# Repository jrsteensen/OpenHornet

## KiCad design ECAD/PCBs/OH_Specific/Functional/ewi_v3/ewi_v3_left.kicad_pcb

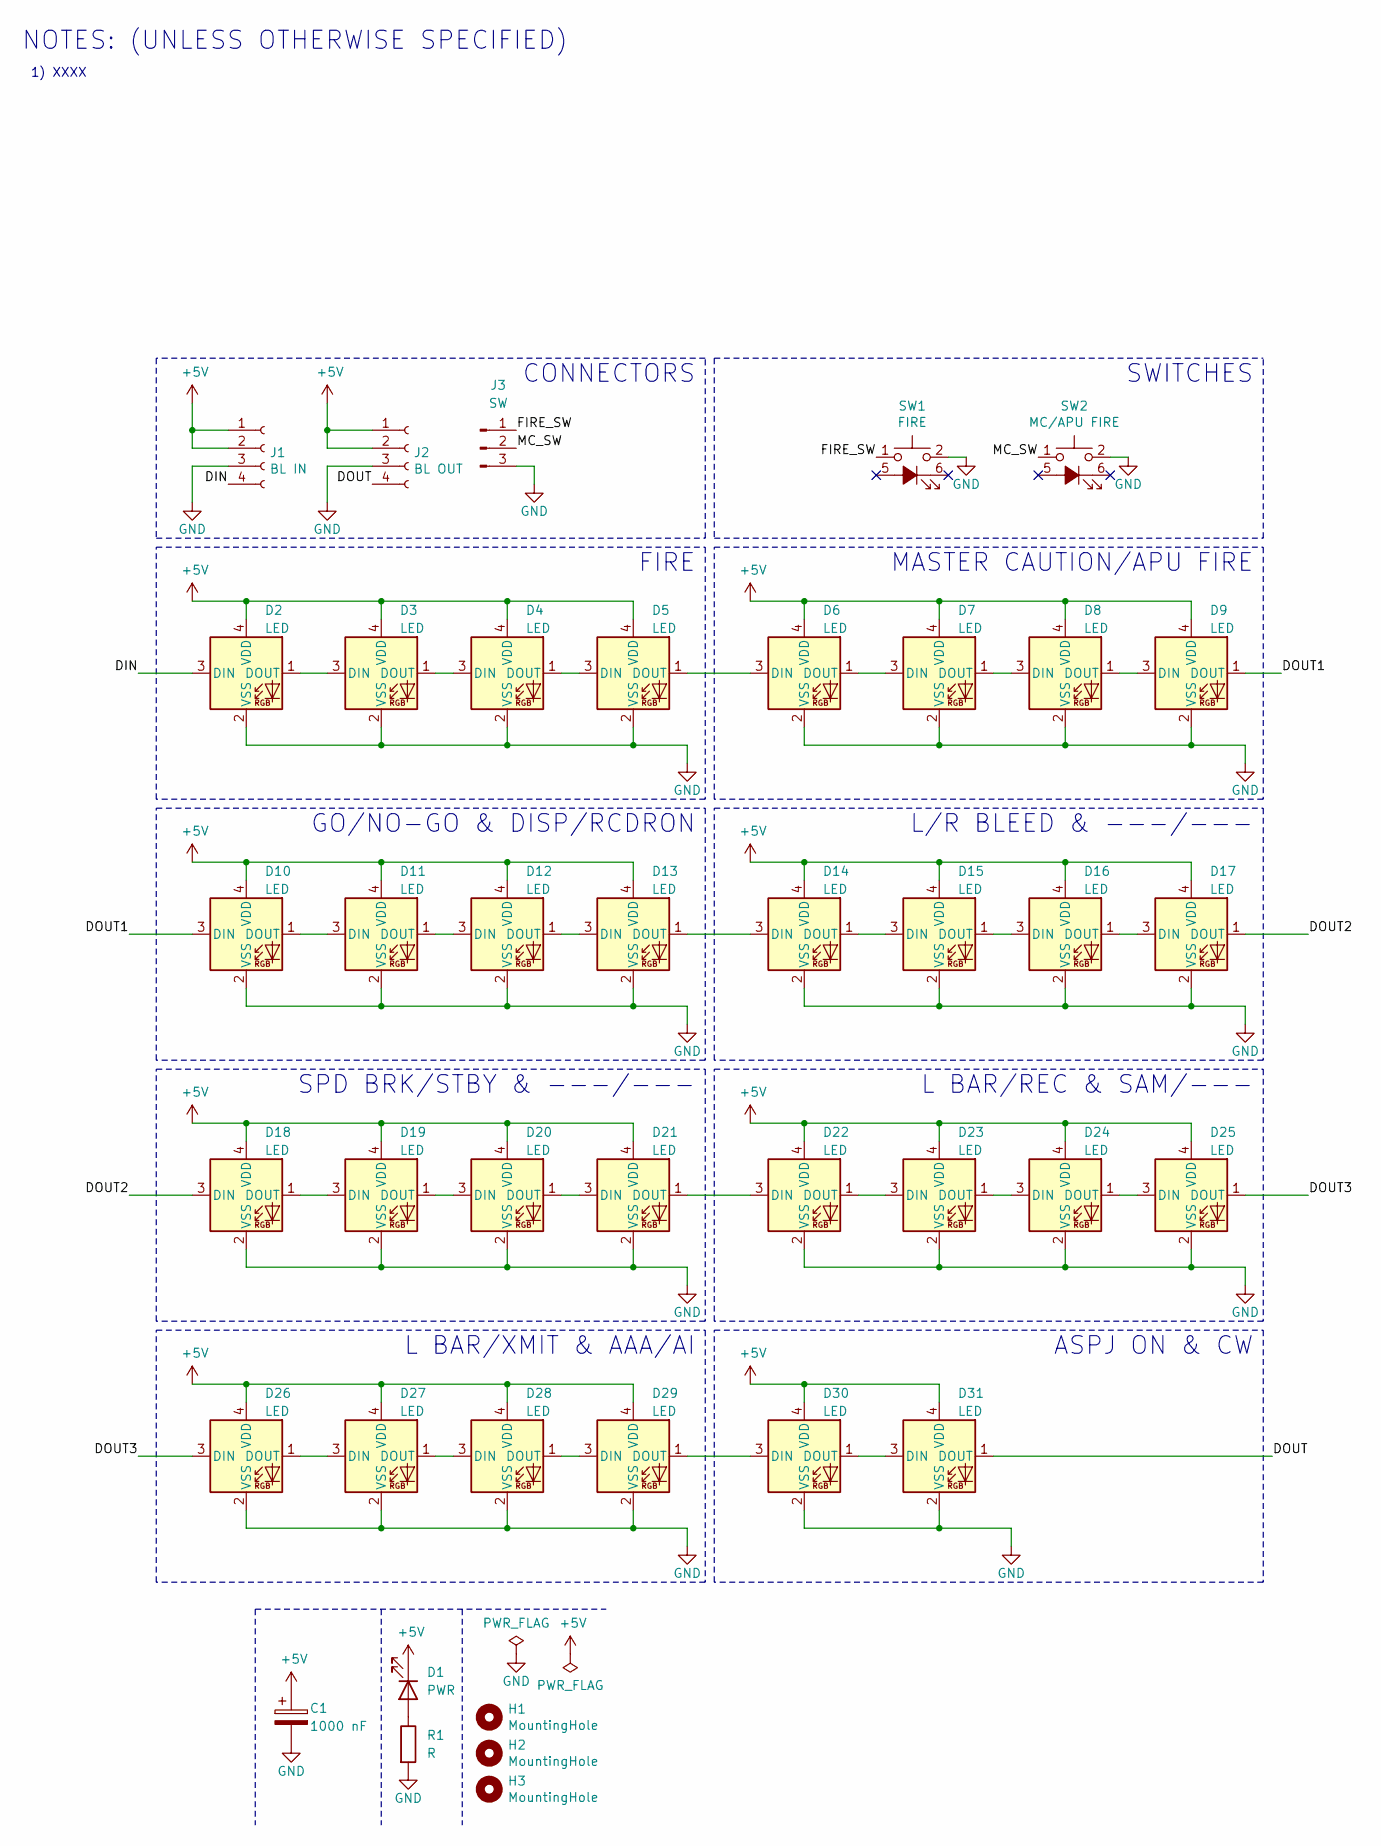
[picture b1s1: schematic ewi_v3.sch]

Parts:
C1: 1000 nF; CP_Elec_8x10; LCSC C134755
D1: PWR; LED_D3.0mm
D2, D3, D4, D5, D6, D7, D8, D9, D10, D11, D12, D13, D14, D15, D16, D17, D18, D19, D20, D21, D22, D23, D24, D25, D26, D27, D28, D29, D30, D31: LED; WS2812-2020; LCSC C965555
H1, H2, H3: MountingHole; MountingHole_2.5mm
J1: BL IN; Molex_Mini-Fit_Jr_5566-04A_2x02_P4.20mm_Vertical
J2: BL OUT; Molex_Mini-Fit_Jr_5566-04A_2x02_P4.20mm_Vertical
J3: SW; Molex_KK-254_AE-6410-03A_1x03_P2.54mm_Vertical; LCSC C471416
R1: R; R_0603_1608Metric
SW1: FIRE; TL1240GQ
SW2: MC/APU FIRE; TL1240GQ

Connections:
+5V: C1.1, D1.1 (K), D2.4 (VDD), D3.4 (VDD), D4.4 (VDD), D5.4 (VDD), D6.4 (VDD), D7.4 (VDD), D8.4 (VDD), D9.4 (VDD), D10.4 (VDD), D11.4 (VDD), D12.4 (VDD), D13.4 (VDD), D14.4 (VDD), D15.4 (VDD), D16.4 (VDD), D17.4 (VDD), D18.4 (VDD), D19.4 (VDD), D20.4 (VDD), D21.4 (VDD), D22.4 (VDD), D23.4 (VDD), D24.4 (VDD), D25.4 (VDD), D26.4 (VDD), D27.4 (VDD), D28.4 (VDD), D29.4 (VDD), D30.4 (VDD), D31.4 (VDD), J1.1, J1.2, J2.1, J2.2
/DIN: D2.3 (DIN), J1.4
/DOUT: D31.1 (DOUT), J2.4
/DOUT1: D9.1 (DOUT), D10.3 (DIN)
/DOUT2: D17.1 (DOUT), D18.3 (DIN)
/DOUT3: D25.1 (DOUT), D26.3 (DIN)
/FIRE_SW: J3.1, SW1.1
/MC_SW: J3.2, SW2.1
GND: C1.2, D2.2 (VSS), D3.2 (VSS), D4.2 (VSS), D5.2 (VSS), D6.2 (VSS), D7.2 (VSS), D8.2 (VSS), D9.2 (VSS), D10.2 (VSS), D11.2 (VSS), D12.2 (VSS), D13.2 (VSS), D14.2 (VSS), D15.2 (VSS), D16.2 (VSS), D17.2 (VSS), D18.2 (VSS), D19.2 (VSS), D20.2 (VSS), D21.2 (VSS), D22.2 (VSS), D23.2 (VSS), D24.2 (VSS), D25.2 (VSS), D26.2 (VSS), D27.2 (VSS), D28.2 (VSS), D29.2 (VSS), D30.2 (VSS), D31.2 (VSS), J1.3, J2.3, J3.3, R1.2, SW1.2, SW2.2
unnamed: D1.2 (A), R1.1
unnamed: D2.1 (DOUT), D3.3 (DIN)
unnamed: D3.1 (DOUT), D4.3 (DIN)
unnamed: D4.1 (DOUT), D5.3 (DIN)
unnamed: D5.1 (DOUT), D6.3 (DIN)
unnamed: D6.1 (DOUT), D7.3 (DIN)
unnamed: D7.1 (DOUT), D8.3 (DIN)
unnamed: D8.1 (DOUT), D9.3 (DIN)
unnamed: D10.1 (DOUT), D11.3 (DIN)
unnamed: D11.1 (DOUT), D12.3 (DIN)
unnamed: D12.1 (DOUT), D13.3 (DIN)
unnamed: D13.1 (DOUT), D14.3 (DIN)
unnamed: D14.1 (DOUT), D15.3 (DIN)
unnamed: D15.1 (DOUT), D16.3 (DIN)
unnamed: D16.1 (DOUT), D17.3 (DIN)
unnamed: D18.1 (DOUT), D19.3 (DIN)
unnamed: D19.1 (DOUT), D20.3 (DIN)
unnamed: D20.1 (DOUT), D21.3 (DIN)
unnamed: D21.1 (DOUT), D22.3 (DIN)
unnamed: D22.1 (DOUT), D23.3 (DIN)
unnamed: D23.1 (DOUT), D24.3 (DIN)
unnamed: D24.1 (DOUT), D25.3 (DIN)
unnamed: D26.1 (DOUT), D27.3 (DIN)
unnamed: D27.1 (DOUT), D28.3 (DIN)
unnamed: D28.1 (DOUT), D29.3 (DIN)
unnamed: D29.1 (DOUT), D30.3 (DIN)
unnamed: D30.1 (DOUT), D31.3 (DIN)

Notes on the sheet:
NOTES: (UNLESS OTHERWISE SPECIFIED)
1) XXXX
FIRE
MASTER CAUTION/APU FIRE
GO/NO-GO & DISP/RCDRON
L/R BLEED & ---/---
SPD BRK/STBY & ---/---
L BAR/XMIT & AAA/AI
ASPJ ON & CW
L BAR/REC & SAM/---
SWITCHES
CONNECTORS

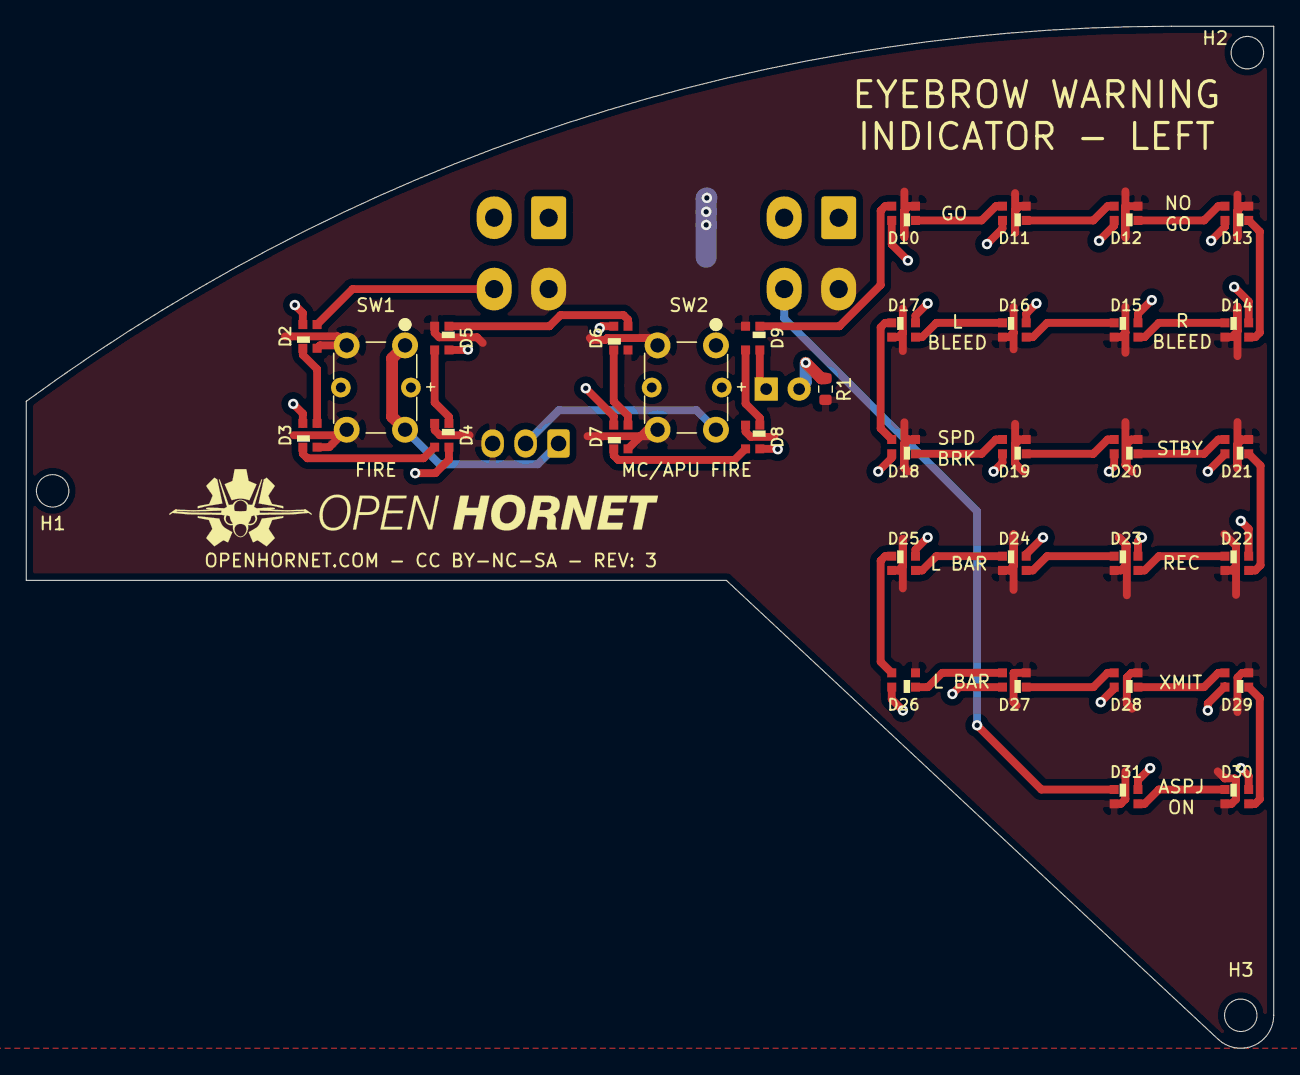
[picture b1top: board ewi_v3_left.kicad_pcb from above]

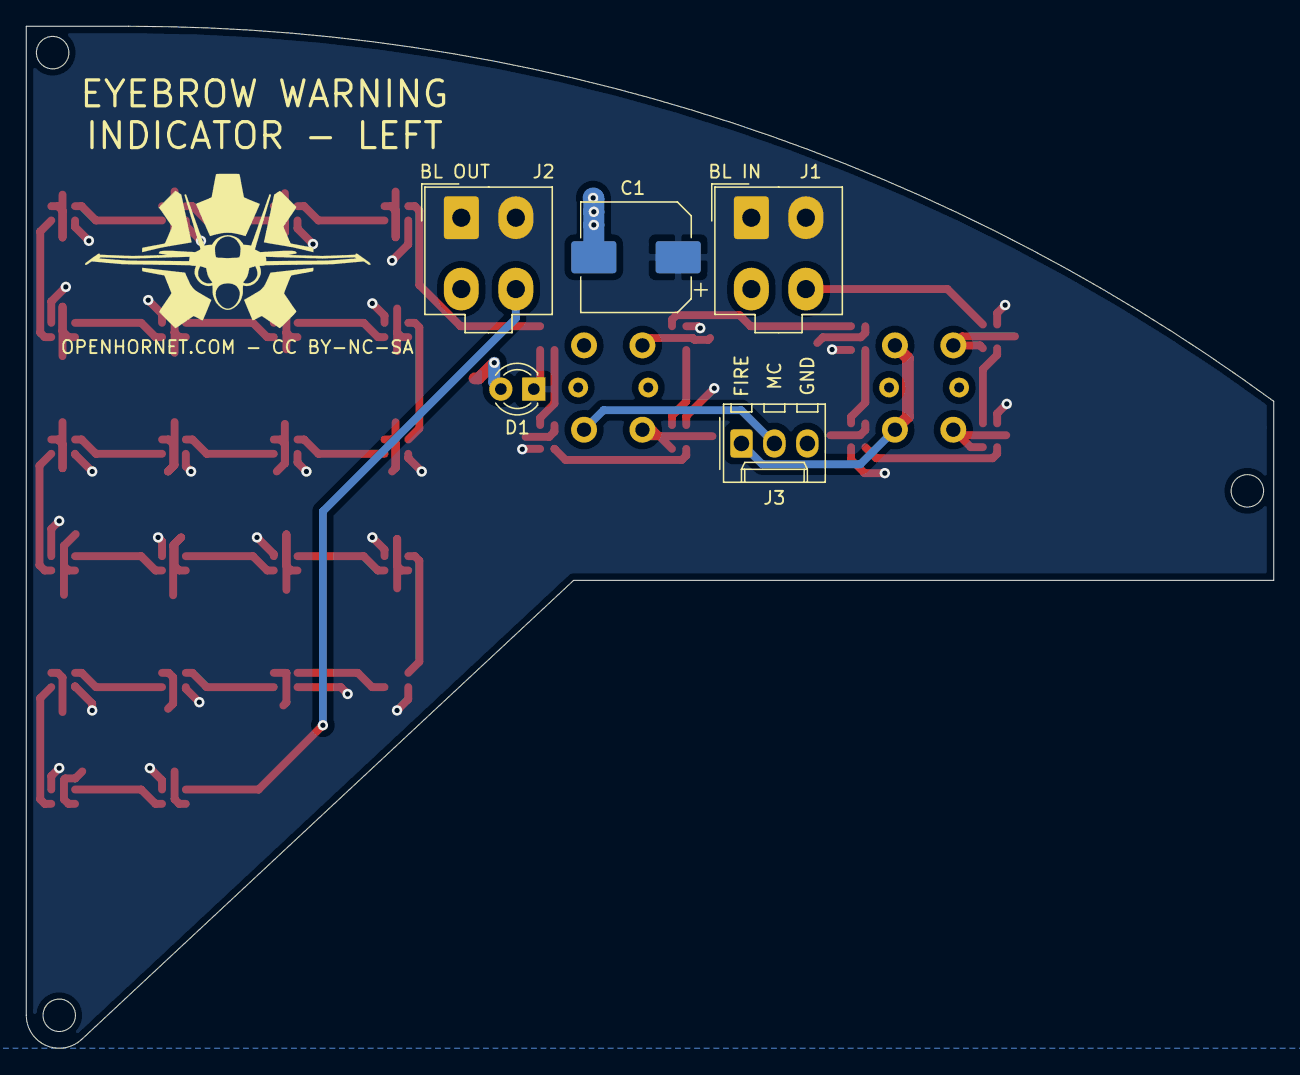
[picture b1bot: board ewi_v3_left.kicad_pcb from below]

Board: 2 copper layers, 96.1 x 78.8 mm, 41 parts (5 on the bottom side), 36 nets.

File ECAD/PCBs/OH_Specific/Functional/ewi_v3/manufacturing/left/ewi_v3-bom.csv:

Comment,Designator,Footprint,LCSC
"1000 nF","C1","Capacitor_SMD:CP_Elec_8x10",""
"PWR","D1","LED_THT:LED_D3.0mm",""
"LED","D2,D3,D4,D5,D6,D7,D8,D9,D10,D11,D12,D13,D14,D15,D16,D17,D18,D19,D20,D21,D22,D23,D24,D25,D26,D27,D28,D29,D30,D31","KiCAD_Libraries:WS2812-2020","C965555"
"MountingHole","H1,H2,H3","MountingHole:MountingHole_2.5mm",""
"BL IN","J1","Connector_Molex:Molex_Mini-Fit_Jr_5566-04A_2x02_P4.20mm_Vertical",""
"BL OUT","J2","Connector_Molex:Molex_Mini-Fit_Jr_5566-04A_2x02_P4.20mm_Vertical",""
"SW","J3","Connector_Molex:Molex_KK-254_AE-6410-03A_1x03_P2.54mm_Vertical","C471416"
"R","R1","Resistor_SMD:R_0603_1608Metric",""
"FIRE","SW1","KiCAD_Libraries:TL1240GQ",""
"MC/APU FIRE","SW2","KiCAD_Libraries:TL1240GQ",""

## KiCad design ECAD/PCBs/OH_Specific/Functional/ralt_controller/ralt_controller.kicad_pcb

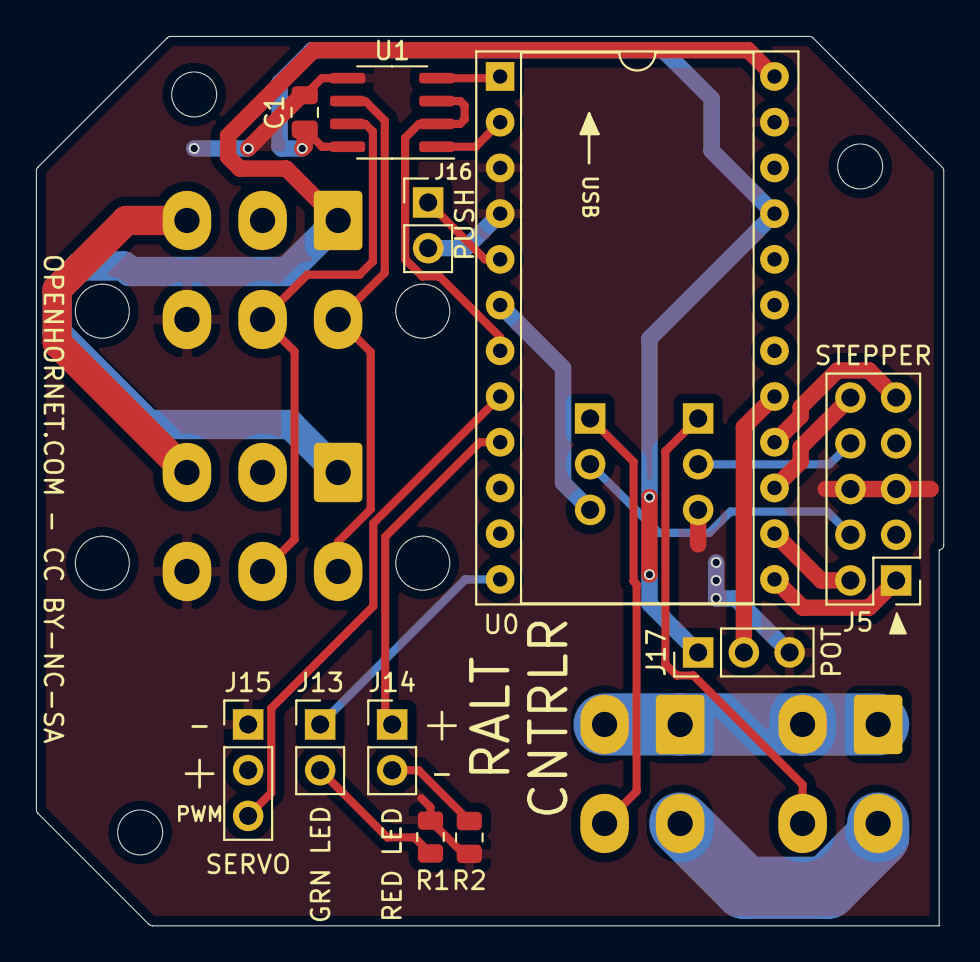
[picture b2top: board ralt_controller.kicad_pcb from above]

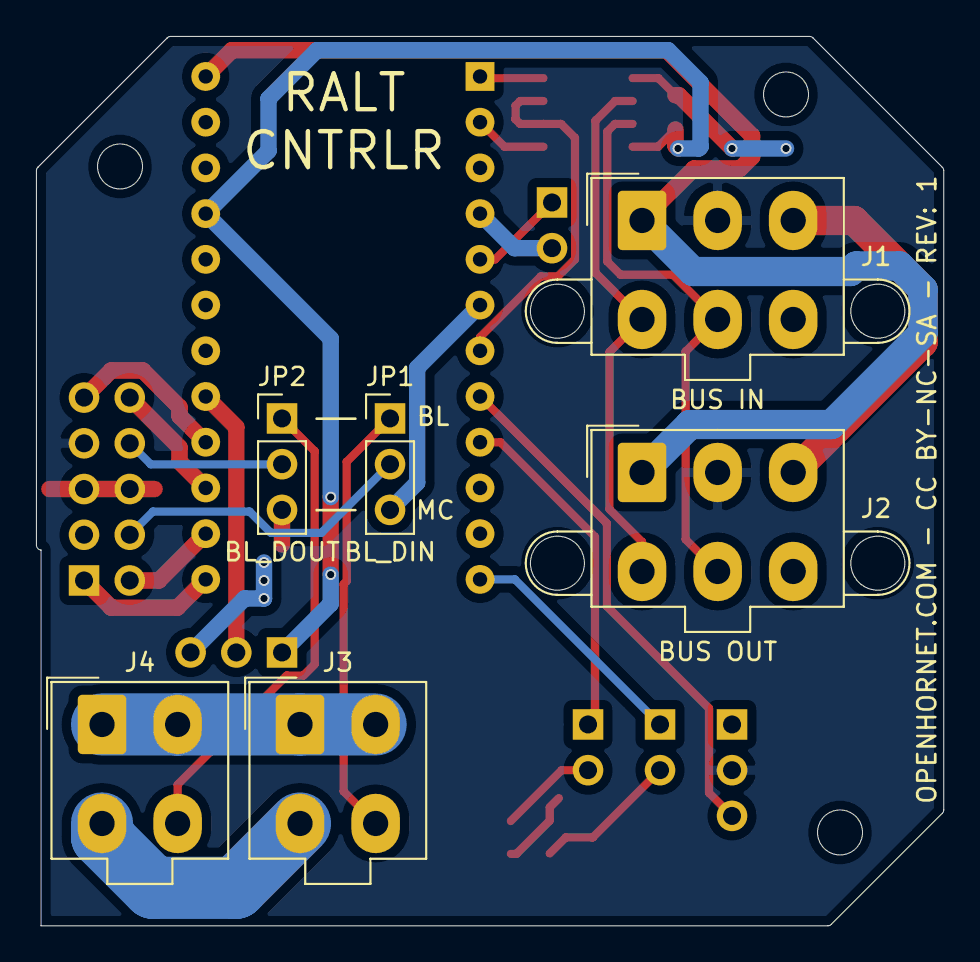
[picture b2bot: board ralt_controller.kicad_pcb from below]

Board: 2 copper layers, 50.4 x 49.4 mm, 20 parts (6 on the bottom side), 28 nets.

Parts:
C1: 0.1uF; C_0805_2012Metric
J1: BUS IN; Molex_Mini-Fit_Jr_5566-06A2_2x03_P4.20mm_Vertical
J2: BUS OUT; Molex_Mini-Fit_Jr_5566-06A2_2x03_P4.20mm_Vertical
J3: BL IN; Molex_Mini-Fit_Jr_5566-04A_2x02_P4.20mm_Vertical
J4: BL OUT; Molex_Mini-Fit_Jr_5566-04A_2x02_P4.20mm_Vertical
J5: STEPPER; PinHeader_2x05_P2.54mm_Vertical
J13: GRN LED; PinHeader_1x02_P2.54mm_Vertical
J14: RED LED; PinHeader_1x02_P2.54mm_Vertical
J15: SERVO; PinHeader_1x03_P2.54mm_Vertical
J16: PUSH; PinHeader_1x02_P2.54mm_Vertical
J17: POT; PinHeader_1x03_P2.54mm_Vertical
JP1: BL_DIN; PinHeader_1x03_P2.54mm_Vertical
JP2: BL_DOUT; PinHeader_1x03_P2.54mm_Vertical
MK1, MK2, MK3: MH; MountingHole_2.5mm
R1, R2: 120; R_0805_2012Metric
U0: ProMicro; DIP-24_W15.24mm_Socket
U1: MAX487EESA+T; SOIC-8_3.9x4.9mm_P1.27mm

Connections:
+5V: C1.1, J17.1, U0.21, U1.8
/+3.3V_SUPPLY: J1.3, J2.3
/+5V_SUPPLY: J1.2, J2.2, J5.7, J15.2
/+12V_SUPPLY: J1.1, J2.1, U0.24
/A0: J17.2, U0.17
/BUS-A: J1.4, J2.4, U1.6
/BUS-B: J1.5, J2.5, U1.7
/D4A6: U0.7, U1.2, U1.3
/D14MISO: J5.10, U0.15
/D15SCK: J5.9, U0.16
/D16MOSI: J5.2, U0.14
/DATAIN: J3.4, JP1.1
/DATAOUT: J4.4, JP2.1
/LED+5V: J3.1, J3.2, J4.1, J4.2
/LEDGND: J3.3, J4.3
/LED_DIN: J5.4, JP1.2
/LED_DOUT: J5.8, JP2.2
/RX1D0: U0.2, U1.1
/SDAD2: J16.1, U0.5
/TX0D1: U0.1, U1.4
/~D5: J15.3, U0.8
/~D6A7: J14.1, U0.9
/~D9A9: J13.1, U0.12
/~D10A10: J5.1, U0.13
/~SCLD3: JP1.3, U0.6
GND: C1.2, J1.6, J2.6, J5.5, J5.6, J15.1, J16.2, J17.3, JP2.3, R1.1, R2.1, U0.3, U0.4, U0.23, U1.5
unnamed: J13.2, R1.2
unnamed: J14.2, R2.2

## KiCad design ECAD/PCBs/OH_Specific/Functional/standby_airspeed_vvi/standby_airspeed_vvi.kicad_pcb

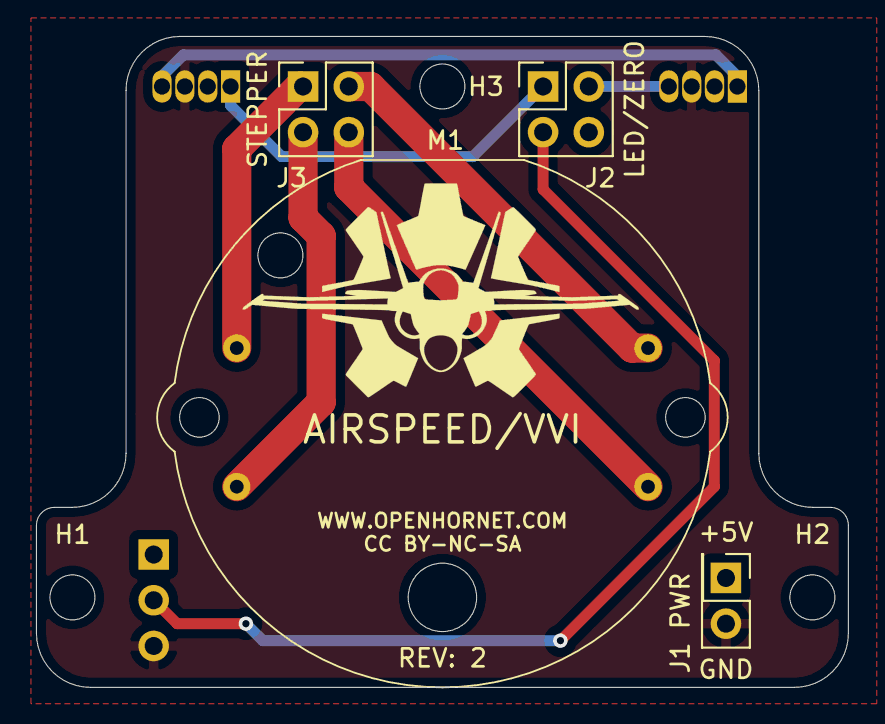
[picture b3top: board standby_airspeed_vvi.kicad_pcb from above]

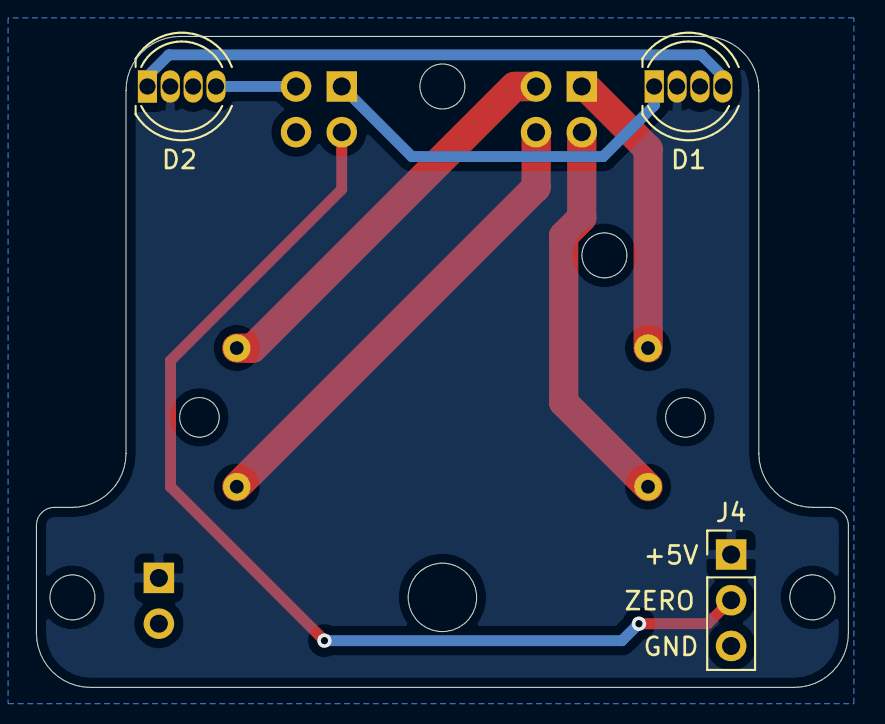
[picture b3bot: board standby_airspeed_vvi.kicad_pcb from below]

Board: 2 copper layers, 45.1 x 36.2 mm, 10 parts (3 on the bottom side), 10 nets.

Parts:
D1, D2: 1938; LED_D5.0mm-4_RGB
H1, H2, H3: MountingHole; MountingHole_2.5mm
J1: PWR; PinHeader_2x01_P2.54mm_Vertical
J2: LED/ZERO; PinHeader_2x02_P2.54mm_Vertical
J3: STEPPER; PinHeader_2x02_P2.54mm_Vertical
J4: ZERO; PinHeader_1x03_P2.54mm_Vertical
M1: VID29-02

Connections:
+5V: D1.2, D2.2, J1.1, J4.1
/COIL1: J3.1, M1.1
/COIL2: J3.3, M1.2
/COIL3: J3.4, M1.3
/COIL4: J3.2, M1.4
/LED_DIN: D1.1, J2.1
/LED_DOUT: D2.4, J2.2
/ZERO_DETECT: J2.3, J4.2
GND: D1.3, D2.3, J1.2, J4.3
unnamed: D1.4, D2.1

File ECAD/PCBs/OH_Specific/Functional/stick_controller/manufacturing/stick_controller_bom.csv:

Comment,Designator,Footprint,LCSC
MountingHole,"H1,H2",MountingHole:MountingHole_2.5mm,
X/ROLL,J1,Connector_JST:JST_PH_S6B-PH-K_1x06_P2.00mm_Horizontal,C265105
Y/PITCH,J2,Connector_JST:JST_PH_S6B-PH-K_1x06_P2.00mm_Horizontal,C265105
Z/AUX,J3,Connector_JST:JST_PH_S6B-PH-K_1x06_P2.00mm_Horizontal,C265105
TM GRIP,J4,Connector_JST:JST_PH_S5B-PH-K_1x05_P2.00mm_Horizontal,C157923
OpenHornetLogoSmall,LOGO1,KiCAD Libraries:OH_LOGO_37.7mm_5.9mm,
OpenHornetLogoSmall,LOGO2,KiCAD Libraries:CC-BY-NC-SA-Small,
ProMicro,U1,Package_DIP:DIP-24_W15.24mm_Socket,C72120

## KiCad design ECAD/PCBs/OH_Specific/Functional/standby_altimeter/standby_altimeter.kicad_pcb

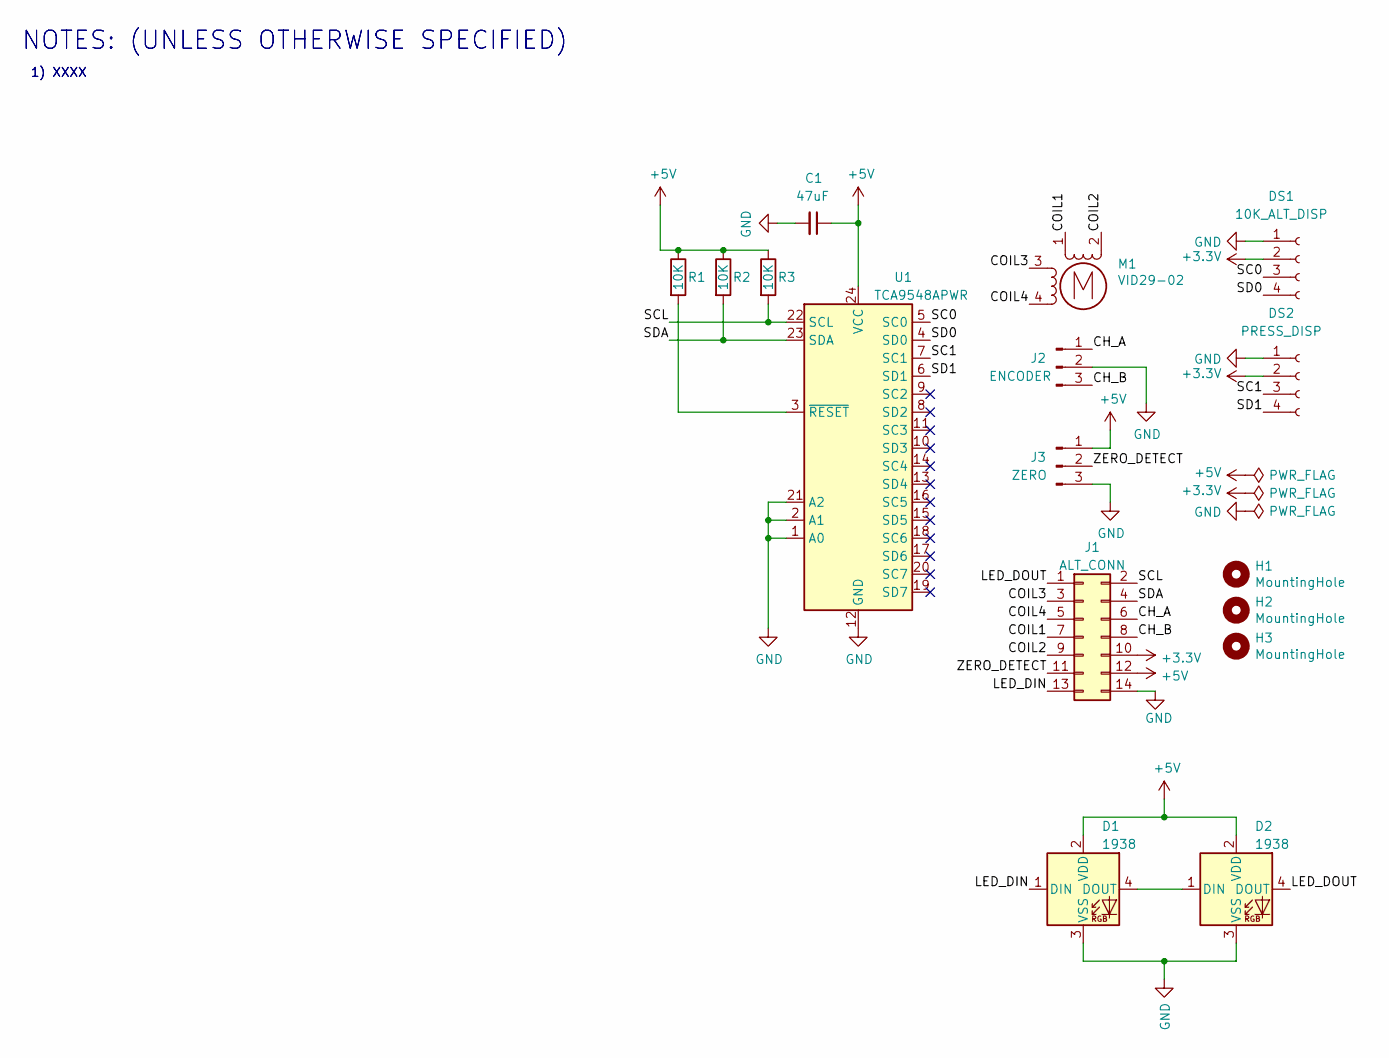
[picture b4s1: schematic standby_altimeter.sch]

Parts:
C1: 47uF; C_1206_3216Metric; LCSC C96123
D1, D2: 1938; LED_D5.0mm-4_RGB
DS1: 10K_ALT_DISP; PinSocket_1x04_P2.54mm_Vertical
DS2: PRESS_DISP; PinSocket_1x04_P2.54mm_Vertical
H1, H2, H3: MountingHole; MountingHole_2.5mm
J1: ALT_CONN; PinHeader_2x07_P2.54mm_Vertical
J2: ENCODER; PinHeader_1x03_P2.54mm_Vertical
J3: ZERO; PinHeader_1x03_P2.54mm_Vertical
M1: VID29-02
R1, R2, R3: 10K; R_0603_1608Metric; LCSC C25804
U1: TCA9548APWR; TSSOP-24_4.4x7.8mm_P0.65mm; LCSC C130026

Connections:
+3V3: DS1.2, DS2.2, J1.10
+5V: C1.1, D1.2 (VDD), D2.2 (VDD), J1.12, J3.1, R1.1, R2.1, R3.1, U1.24 (VCC)
/CH_A: J1.6, J2.1
/CH_B: J1.8, J2.3
/COIL1: J1.7, M1.1
/COIL2: J1.9, M1.2 (-)
/COIL3: J1.3, M1.3
/COIL4: J1.5, M1.4
/LED_DIN: D1.1 (DIN), J1.13
/LED_DOUT: D2.4 (DOUT), J1.1
/SC0: DS1.3, U1.5 (SC0)
/SC1: DS2.3, U1.7 (SC1)
/SCL: J1.2, R3.2, U1.22 (SCL)
/SD0: DS1.4, U1.4 (SD0)
/SD1: DS2.4, U1.6 (SD1)
/SDA: J1.4, R2.2, U1.23 (SDA)
/ZERO_DETECT: J1.11, J3.2
GND: C1.2, D1.3 (VSS), D2.3 (VSS), DS1.1, DS2.1, J1.14, J2.2, J3.3, U1.1 (A0), U1.2 (A1), U1.12 (GND), U1.21 (A2)
unnamed: D1.4 (DOUT), D2.1 (DIN)
unnamed: R1.2, U1.3 (~RESET)

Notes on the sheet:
NOTES: (UNLESS OTHERWISE SPECIFIED)
1) XXXX

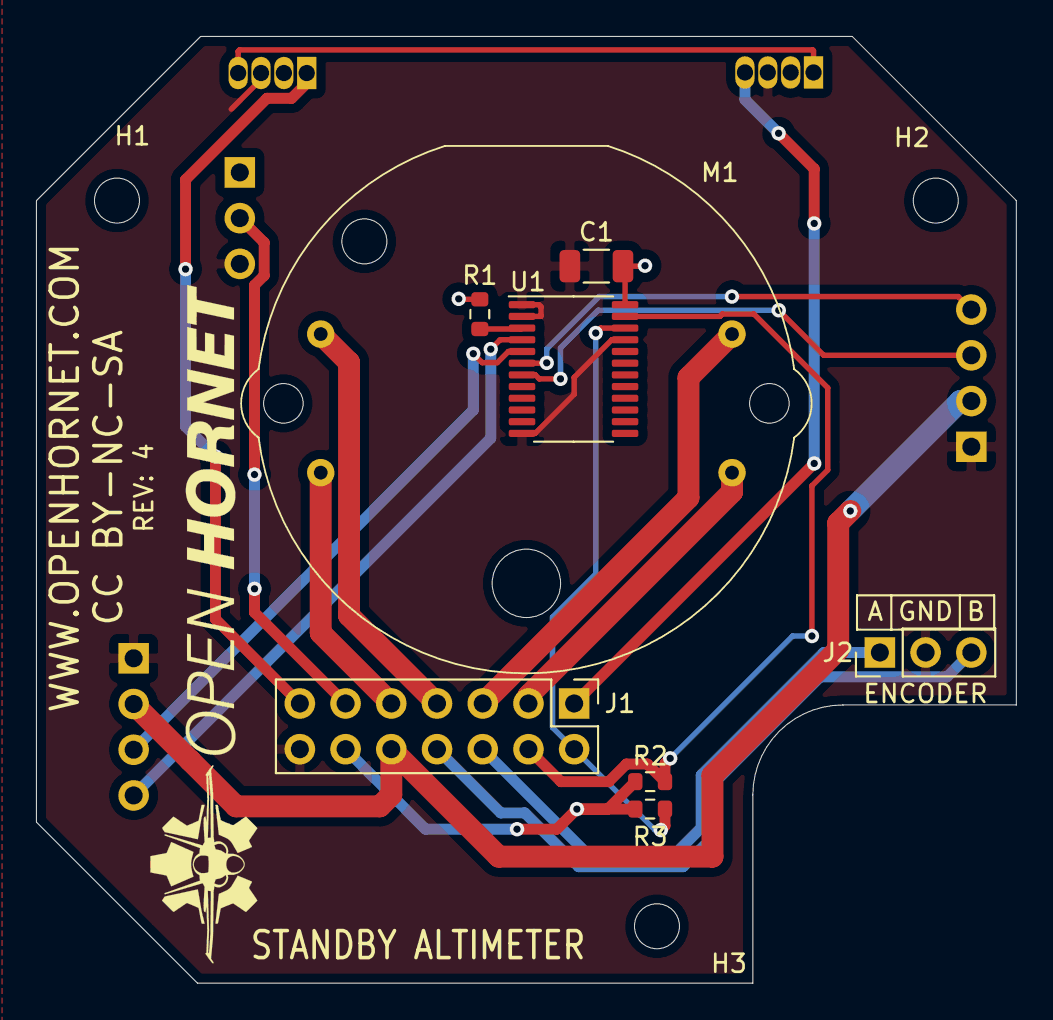
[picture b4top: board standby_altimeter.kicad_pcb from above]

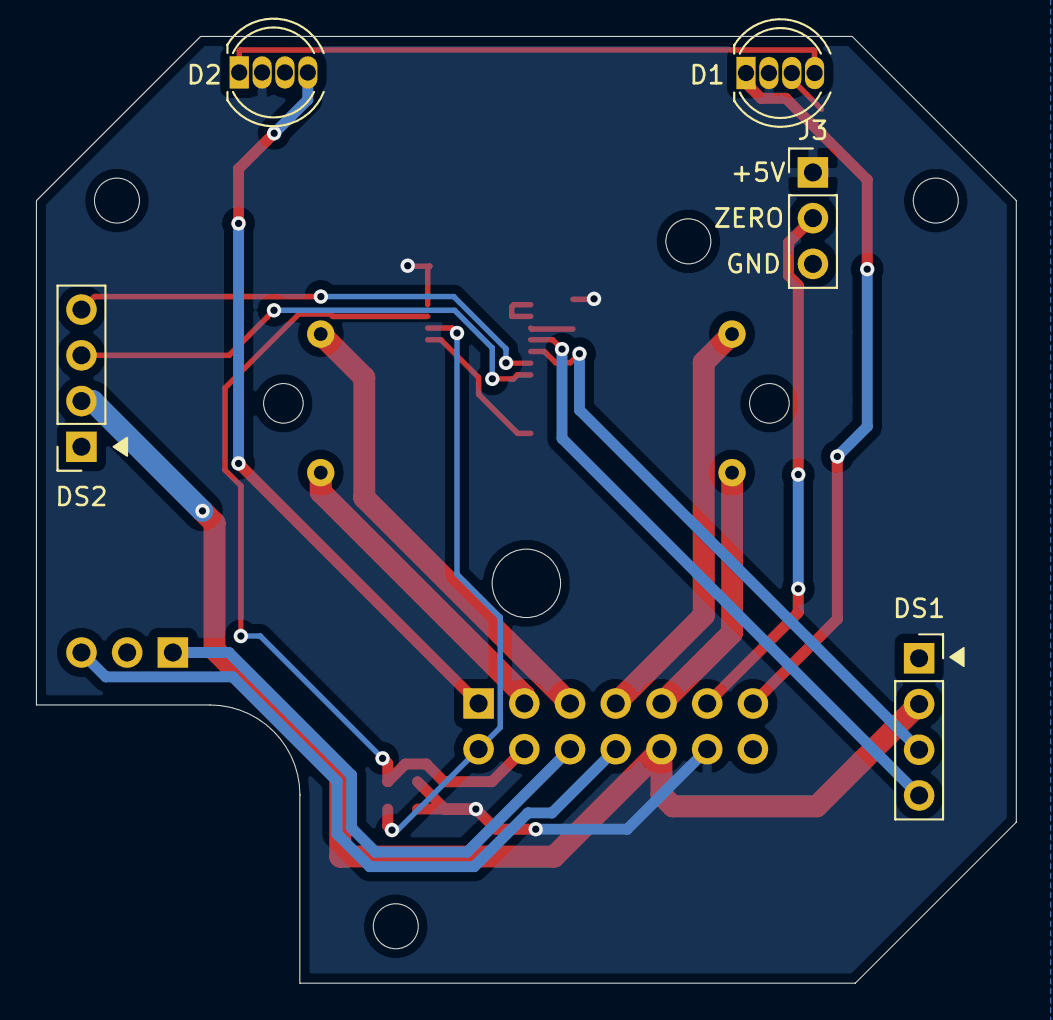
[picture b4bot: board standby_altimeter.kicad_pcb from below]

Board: 2 copper layers, 54.4 x 52.6 mm, 16 parts (5 on the bottom side), 20 nets.

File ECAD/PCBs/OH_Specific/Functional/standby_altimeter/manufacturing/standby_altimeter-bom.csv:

Comment,Designator,Footprint,LCSC
"47uF","C1","Capacitor_SMD:C_1206_3216Metric","C96123"
"10K_ALT_DISP","DS1","Connector_PinSocket_2.54mm:PinSocket_1x04_P2.54mm_Vertical",""
"PRESS_DISP","DS2","Connector_PinSocket_2.54mm:PinSocket_1x04_P2.54mm_Vertical",""
"MountingHole","H1,H2,H3","MountingHole:MountingHole_2.5mm",""
"ALT_CONN","J1","Connector_PinHeader_2.54mm:PinHeader_2x06_P2.54mm_Vertical",""
"ENCODER","J2","Connector_PinHeader_2.54mm:PinHeader_1x03_P2.54mm_Vertical",""
"ZERO","J3","Connector_PinHeader_2.54mm:PinHeader_1x03_P2.54mm_Vertical",""
"VID29-02","M1","KiCAD Libraries:VID29-02",""
"10K","R1,R2,R3","Resistor_SMD:R_0603_1608Metric","C25804"
"TCA9548APWR","U1","Package_SO:TSSOP-24_4.4x7.8mm_P0.65mm","C130026"

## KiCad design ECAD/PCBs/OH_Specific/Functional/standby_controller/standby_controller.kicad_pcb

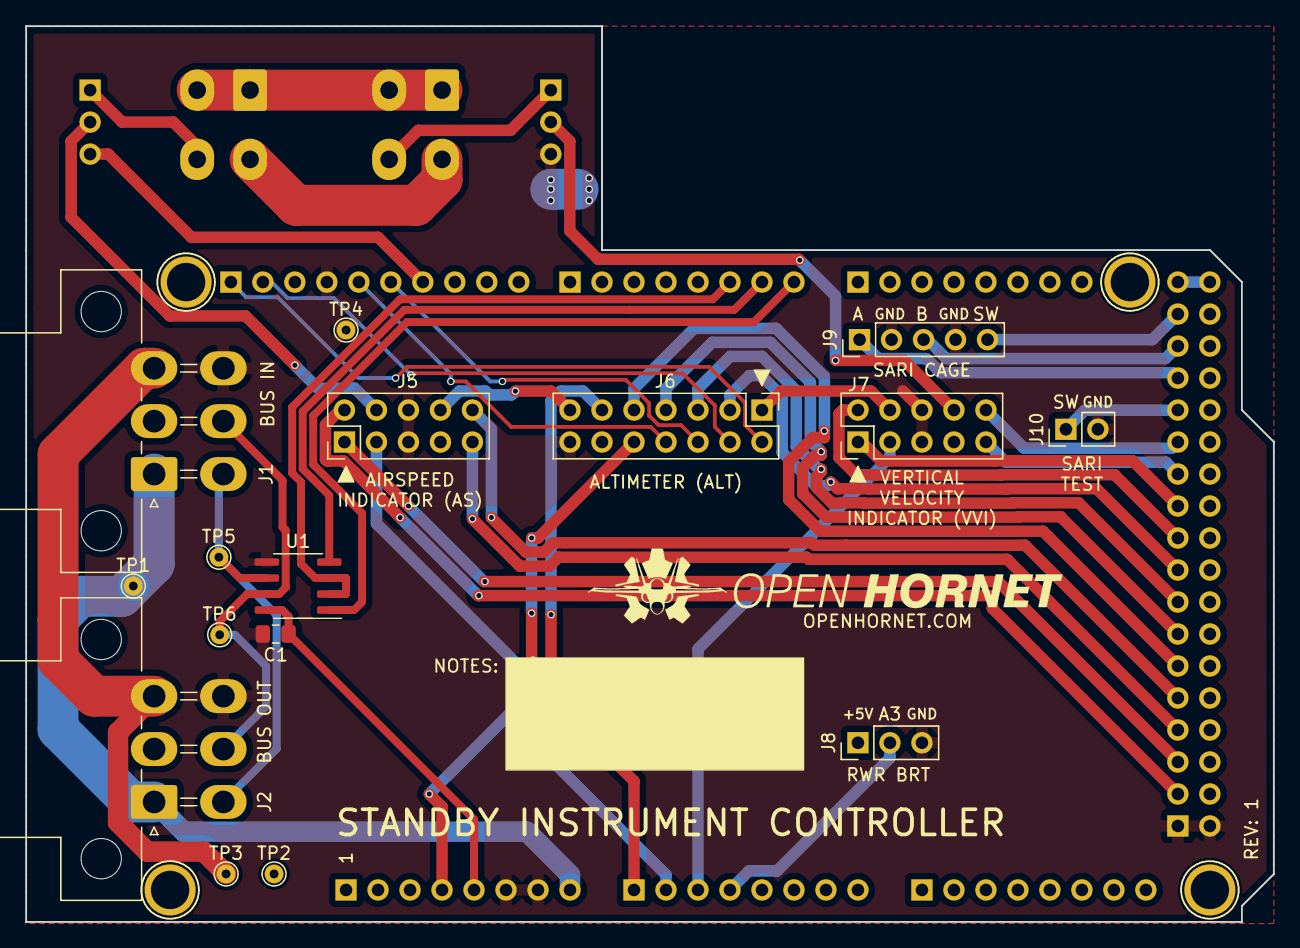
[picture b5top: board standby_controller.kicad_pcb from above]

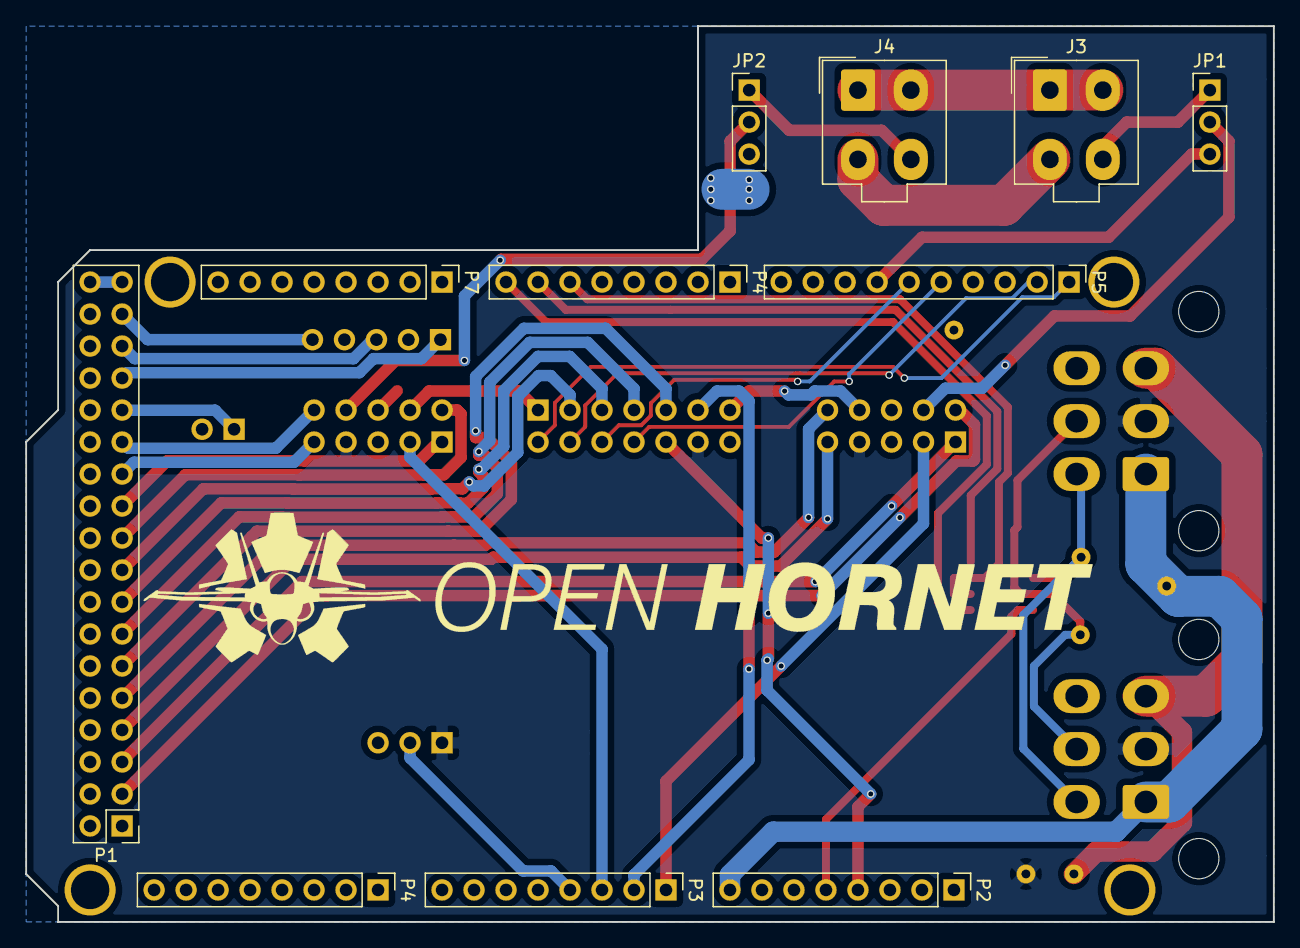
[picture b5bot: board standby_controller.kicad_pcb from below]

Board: 2 copper layers, 99.1 x 71.1 mm, 31 parts (11 on the bottom side), 45 nets.

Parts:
C1: 0.1uF; C_0805_2012Metric_Pad1.15x1.40mm_HandSolder
J1: BUS IN; Molex_Mini-Fit_Jr_5569-06A1_2x03_P4.20mm_Horizontal
J2: BUS OUT; Molex_Mini-Fit_Jr_5569-06A1_2x03_P4.20mm_Horizontal
J3: BL IN; Molex_Mini-Fit_Jr_5566-04A_2x02_P4.20mm_Vertical
J4: BL OUT; Molex_Mini-Fit_Jr_5566-04A_2x02_P4.20mm_Vertical
J5: AIRSPEED; PinHeader_2x05_P2.54mm_Vertical
J6: ALTIMETER; PinHeader_2x07_P2.54mm_Vertical
J7: VVI; PinHeader_2x05_P2.54mm_Vertical
J8: RWR_BRT; PinHeader_1x03_P2.54mm_Vertical
J9: SARI_CAGE; PinHeader_1x05_P2.54mm_Vertical
J10: SARI_TEST; PinHeader_1x02_P2.54mm_Vertical
JP1: BL_DIN_SEL; PinHeader_1x03_P2.54mm_Vertical
JP2: BL_DOUT_SEL; PinHeader_1x03_P2.54mm_Vertical
MK1, MK3, MK4, MK4#2: MH; Arduino_1pin
P1: Digital; PinHeader_2x18_P2.54mm_Vertical
P2: Power; PinHeader_1x08_P2.54mm_Vertical
P3, P4: Analog; PinHeader_1x08_P2.54mm_Vertical
P4#2: PWM; PinHeader_1x08_P2.54mm_Vertical
P5: PWM; PinHeader_1x10_P2.54mm_Vertical
P7: Communication; PinHeader_1x08_P2.54mm_Vertical
TP1: TP-12; TestPoint_THTPad_D1.5mm_Drill0.7mm
TP2: TP-5V; TestPoint_THTPad_D1.5mm_Drill0.7mm
TP3: TP-3.3V; TestPoint_THTPad_D1.5mm_Drill0.7mm
TP4: TP-GND; TestPoint_THTPad_D1.5mm_Drill0.7mm
TP5: TP-A; TestPoint_THTPad_D1.5mm_Drill0.7mm
TP6: TP-B; TestPoint_THTPad_D1.5mm_Drill0.7mm
U1: MAX487EESA+T; SOIC-8_3.9x4.9mm_P1.27mm

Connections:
+3V3: J6.10, P2.4
+5V: C1.1, P2.5, U1.8
+5VD: P1.35, P1.36
/0(Rx0): P4#2.8, U1.1
/1(Tx0): P4#2.7, U1.4
/2(**): P4#2.6, U1.2, U1.3
/11(**): JP1.3, P5.7
/12(**): J6.6, P5.6
/13(**): J6.8, P5.5
/22: J9.5, P1.33
/24: J9.3, P1.31
/26: J9.1, P1.29
/28: J10.1, P1.27
/30: J7.10, P1.25
/32: J7.9, P1.23
/34: J7.1, P1.21
/36: J7.2, P1.19
/38: J6.3, P1.17
/40: J6.5, P1.15
/42: J6.7, P1.13
/44: J6.9, P1.11
/46: J5.10, P1.9
/48: J5.9, P1.7
/50(MISO): J5.1, P1.5
/52(SCK): J5.2, P1.3
/+3.3V_SUPPLY: J1.3, J2.3, TP3.1
/+5V_SUPPLY: J1.2, J2.2, J5.7, J6.12, J7.7, J8.1, TP2.1
/+12V_SUPPLY: J1.1, J2.1, P2.8, TP1.1
/A0: J5.3, P3.1
/A1: J6.11, P3.2
/A2: J7.3, P3.3
/A3: J8.2, P3.4
/BUS-A: J1.4, J2.4, TP5.1, U1.6
/BUS-B: J1.5, J2.5, TP6.1, U1.7
/DATAIN: J3.4, JP1.1
/DATAOUT: J4.4, JP2.1
/LED+5V: J3.1, J3.2, J4.1, J4.2
/LEDGND: J3.3, J4.3
/LED_DIN: J5.4, JP1.2
/LED_DOUT: J7.8, JP2.2
/LED_DOUT1: J5.8, J6.13
/LED_DOUT2: J6.1, J7.4
/SCL: J6.2, P5.1
/SDA: J6.4, P5.2
GND: C1.2, J1.6, J2.6, J5.5, J5.6, J6.14, J7.5, J7.6, J8.3, J9.2, J9.4, J10.2, JP2.3, P1.1, P1.2, P2.6, P2.7, P5.4, TP4.1, U1.5

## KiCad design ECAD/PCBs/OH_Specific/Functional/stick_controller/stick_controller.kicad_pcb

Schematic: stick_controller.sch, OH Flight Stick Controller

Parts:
H1, H2: MountingHole; MountingHole_2.5mm
J1: X/ROLL; JST_PH_S6B-PH-K_1x06_P2.00mm_Horizontal; LCSC C265105
J2: Y/PITCH; JST_PH_S6B-PH-K_1x06_P2.00mm_Horizontal; LCSC C265105
J3: Z/AUX; JST_PH_S6B-PH-K_1x06_P2.00mm_Horizontal; LCSC C265105
J4: TM GRIP; JST_PH_S5B-PH-K_1x05_P2.00mm_Horizontal; LCSC C157923
J5: AUX I/O; PinHeader_2x07_P2.54mm_Vertical
LOGO1: OpenHornetLogoSmall; OH_LOGO_37.7mm_5.9mm
LOGO2: OpenHornetLogoSmall; CC-BY-NC-SA-Small
LOGO3: OpenHornetLogoSmall; OH_LOGO_ONLY_11x6mm
Q1, Q2: IRLML6402TRPBF; SOT-23; LCSC C2593
Q3: 2N7002; SOT-23; LCSC C8545
R1: 10k; R_0603_1608Metric; LCSC C25804
R2: 33; R_0402_1005Metric; LCSC C25105
SW1: RESET; SMD-SW-4_5.1x5.1; LCSC C318884
U1: ProMicro; DIP-24_W15.24mm_Socket; LCSC C72120

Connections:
+5V: J1.1, J2.1, J3.1, J4.1, J5.2, U1.21 (VCC)
/A0: J5.10, U1.17 (A0)
/A1: J5.8, U1.18 (A1)
/A2: J5.6, U1.19 (A2)
/A3: J5.4, U1.20 (A3)
/CSg: J4.2, Q3.1, U1.9 (~D6/A7)
/CSx: J1.5, U1.12 (~D9/A9)
/CSy: J2.5, U1.11 (D8/A8)
/CSz: J3.5, U1.10 (D7)
/D0: J5.3, U1.2 (RX1/D0)
/D1: J5.1, U1.1 (TX0/D1)
/D2: J5.5, U1.5 (SDA/D2)
/D4A6: J5.9, U1.7 (D4/A6)
/MISO: J1.2, J2.2, J3.2, Q1.3, U1.15 (D14/MISO)
/MISOg: J4.4, Q2.3
/MOSI: J1.3, J2.3, J3.3, U1.14 (D16/MOSI)
/RST: SW1.1, U1.22 (RST)
/SCK: J1.4, J2.4, J3.4, J4.3, U1.16 (D15/SCK)
/~D3: J5.7, U1.6 (~SCL/D3)
/~D5: J5.11, U1.8 (~D5)
/~D10A10: J5.12, U1.13 (~D10/A10)
GND: J1.6, J2.6, J3.6, J4.5, J5.13, J5.14, Q3.2, SW1.3, U1.3 (GND), U1.4 (GND), U1.23 (GND)
unnamed: Q1.1, Q2.1, R1.2, R2.1
unnamed: Q1.2, Q2.2, R1.1
unnamed: Q3.3, R2.2

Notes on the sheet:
CONNECT TO PC VIA USB
ADD C1/100pF cap if issues arise
C1 100pF
SHIFT REGISTER SPI DISCONNECT

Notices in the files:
ECAD/PCBs/OH_Specific/Functional/ewi_v3/ewi_v3_left.kicad_pcb:
OPENHORNET.COM - CC BY-NC-SA
OPENHORNET.COM - CC BY-NC-SA - REV: 3
ECAD/PCBs/OH_Specific/Functional/ralt_controller/ralt_controller.kicad_pcb:
OPENHORNET.COM - CC BY-NC-SA - REV: 1
ECAD/PCBs/OH_Specific/Functional/stick_controller/stick_controller.kicad_pcb:
CC BY-NC-SA  REV: 2
